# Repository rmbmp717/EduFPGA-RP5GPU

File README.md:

# EduFPGA-RP5GPU (Verilog HDL & C++ & Python)

## Introduction

EduFPGA-RP5GPU is an educational GPU designed to work with the Raspberry Pi 5.  
The design data runs on the FPGA and includes a PCIe controller.  
Communication with the Raspberry Pi 5 is possible via a PCIe driver.  
The project includes a PCIe driver compatible with the Raspberry Pi 5 and sample Python scripts.

*Note: This project was created for educational and experimental purposes. Product-grade features and performance improvements will be considered in the future.*

## Demo Environment
- Demo setup
- Raspberry Pi 5 + Tang Mega 138K + PCIe adapter board + ASM1182e PCIe repeater board <br>

- ASM1182e PCIe repeater board
- Without using the ASM1182e PCIe repeater board, the Gowin FPGA's PCIe IP is not recognized at RP5 startup.<br>

## GPU
- The design is based on the tiny-gpu project by the following author:
https://github.com/adam-maj/tiny-gpu
- The ISA (instruction set architecture) has been extended to include a floating-point multiplication instruction.
- GPU ISA <br>

## Directories
- GPU design data runnable on FPGA.
- Includes PCIe controller design data runnable on FPGA.
- PCIe driver code compilable on Raspberry Pi 5.
- Sample Python script to operate the GPU.

## Block Diagram
- Overall block diagram <br>

## Delivered Artifacts
- GPU design data (Verilog)
- GPU data memory controller (Verilog)
- Demo board design (KiCAD)
- PCIe driver (C++)
- FPGA-side PCIe controller (Verilog)
- Python program for character image recognition demo
- PCIe Write/Read program (C++)

## Demo Results
- Ran character recognition code on the Raspberry Pi 5.
- Data is transferred to the GPU via PCIe, and DL operations are executed.
- Character image recognition result when running EduGPU_mnist.py <br>

## PCIe IP Settings
- The PCIe IP BAR settings are as follows: <br>

| BAR  | Enabled | Type    | 64 bit | Prefetchable | Size         | Value (Hex) |
|------|---------|---------|--------|--------------|--------------|-------------|
| Bar0 | Yes     | Memory  | Yes    | No           | 1 Kilobyte   | FFFFFC00    |
| Bar2 | Yes     | Memory  | Yes    | No           | 64 Kilobytes | FFFF0000    |
| Bar4 | Yes     | Memory  | Yes    | No           | 2 Kilobytes  | FFFFF800    |

## Demo Board
- Although the tang console has now been released and I no longer plan to use this, I designed a board that can accommodate FPGA sub-boards.
- Designed with KiCAD.
- Compatible with the Tang 138K SOM board.
- (There are wiring correction points)

## Unresolved Issues
- DMA transfer is not yet supported.
- The design has not progressed to the point of using the DDR memory on the FPGA board concurrently with the GPU.

## Future Plans
- After completing minimal operation checks, I consulted with someone at the Sapporo Small and Medium Enterprise Center, and the conclusion was that "it would be difficult to commercialize" (I had explained from the start that this was for educational purposes).
- Once the Sipeed FPGA board (tang console) arrives from a Chinese online store as a replacement for the demo board, I plan to write the existing design data to it, confirm operation, and then wrap up the project.

## Impressions
- I have compiled the past Notes and design data.
- The design period was 2.5 months.
- If you don’t organize things from a year ago, you tend to forget them.

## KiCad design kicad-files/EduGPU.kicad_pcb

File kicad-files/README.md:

# Demo Board

- Although the tang console has now been released and I no longer plan to use this, I designed a board that can accommodate FPGA sub-boards.
- Designed with KiCAD.
- (There are wiring correction points) <br>

- Compatible with the Tang 138K SOM board. <br>

- SOM Back side. <br>

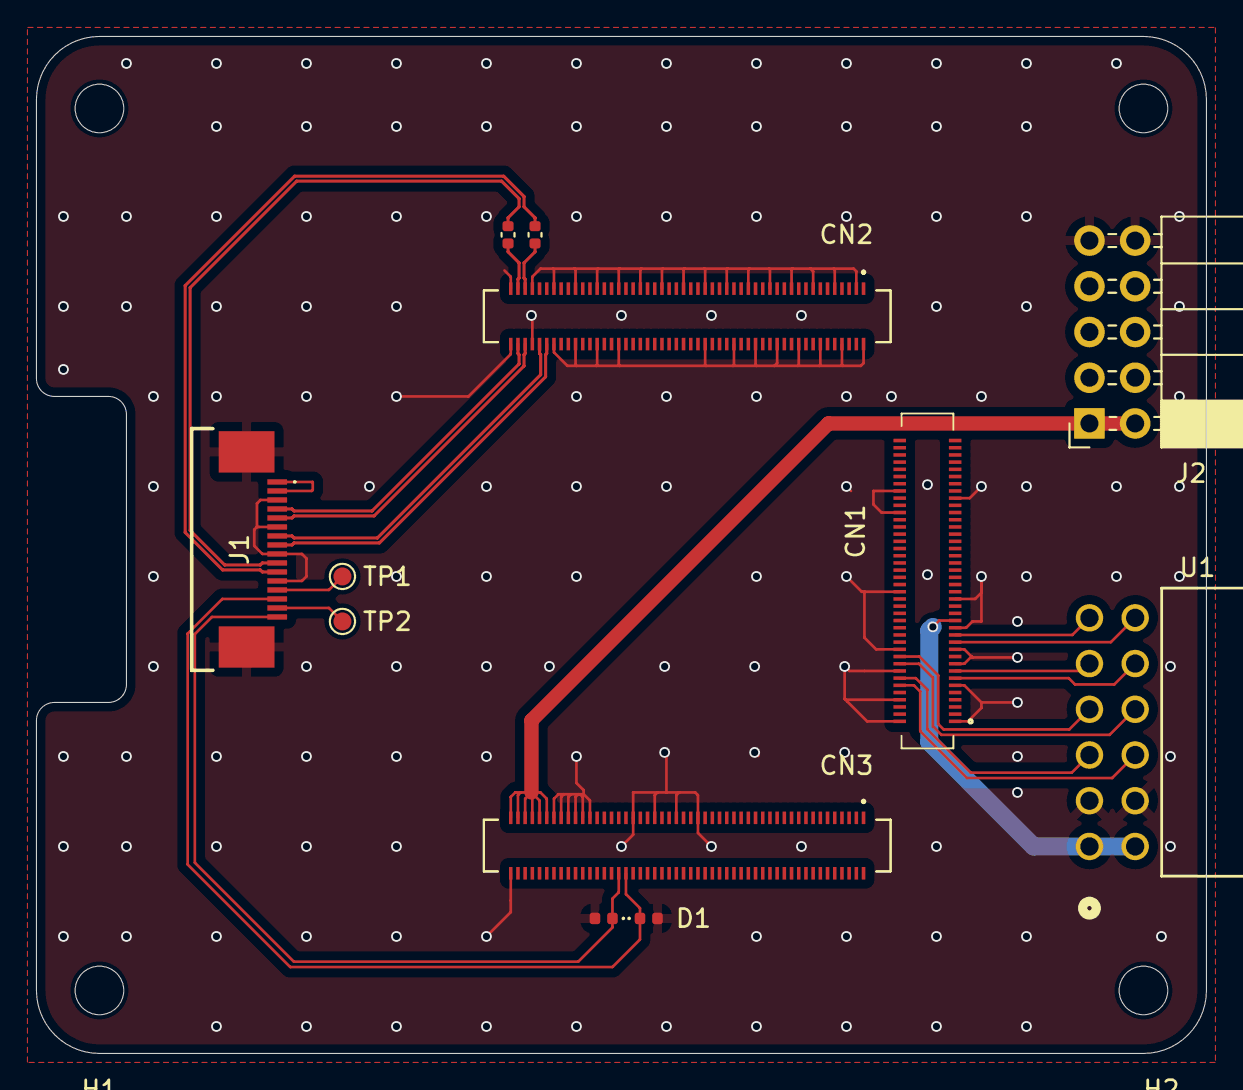
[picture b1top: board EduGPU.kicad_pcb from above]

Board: 4 copper layers, 65.0 x 56.5 mm, 16 parts (0 on the bottom side), 24 nets.

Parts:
C1, C2: GCM155R71C154KE02D; C_0402_1005Metric
CN1: DF40C-80DS-0.4V_58_; DF40C80DS04V58
CN2, CN3: DF40C-100DS-0.4V_58_; DF40C100DS04V58
D1, D2: LXES15AAA1-153; D_0402_1005Metric
H1, H2, H3, H4: MountingHole; MountingHole_2.7mm_M2.5
J1: 1-1734839-6; 117348396
J2: SSW-105-02-G-D; PinSocket_2x05_P2.54mm_Horizontal
TP1: PWR_EN; TestPoint_Pad_D1.0mm
TP2: PCIE_CLKREQ_N; TestPoint_Pad_D1.0mm
U1: PPPC062LJBN-RC; CONN_PPPC062LJBN-RC_SUL_OddEven

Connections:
+3V3: CN1.29, U1.1, U1.2
/PCIE_CLKREQ_N: J1.15, TP2.1
/PWR_EN: J1.13, TP1.1
/TX_N: C1.2, CN2.95
/TX_P: C2.2, CN2.97
DET_WAKE: CN3.68, D1.1, J1.14
GND: CN1.1, CN1.2, CN1.8, CN1.11, CN1.16, CN1.17, CN1.21, CN1.22, CN1.27, CN1.35, CN1.38, CN1.60, CN1.63, CN1.66, CN2.2, CN2.3, CN2.8, CN2.9, CN2.14, CN2.15, CN2.20, CN2.21, CN2.26, CN2.27, CN2.32, CN2.33, CN2.38, CN2.39, CN2.45, CN2.46, CN2.51, CN2.57, CN2.63, CN2.69, CN2.70, CN2.75, CN2.76, CN2.81, CN2.82, CN2.87, CN2.88, CN2.93, CN2.94, CN2.99, CN2.100, CN3.47, CN3.53, CN3.59, CN3.65, CN3.77, CN3.79, CN3.81, CN3.83, CN3.85, CN3.87, CN3.100, D1.2, D2.2, J1.3, J1.6, J1.9, J1.12, J1.17 (MP1), J1.18 (MP2), J2.9, J2.10, U1.3, U1.4
PCIE+5V: J1.1, J1.2
PCIE_CLK_N: CN2.96, J1.5
PCIE_CLK_P: CN2.98, J1.4
PCIE_RST: CN3.70, D2.1, J1.16
PCIE_RX_N: CN2.90, J1.8
PCIE_RX_P: CN2.92, J1.7
PCIE_TX_N: C1.1, J1.11
PCIE_TX_P: C2.1, J1.10
PMOD_IO0: CN1.25, U1.11
PMOD_IO1: CN1.23, U1.12
PMOD_IO2: CN1.15, U1.9
PMOD_IO3: CN1.13, U1.10
PMOD_IO4: CN1.20, U1.7
PMOD_IO5: CN1.18, U1.8
PMOD_IO6: CN1.14, U1.5
PMOD_IO7: CN1.12, U1.6
VCC+5V: CN3.89, CN3.91, CN3.93, CN3.95, CN3.97, CN3.99, J2.1, J2.2

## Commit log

2025-04-25 Rename pcie_tlp_packet_dec .v to pcie_tlp_packet_dec.v
2025-04-25 Rename EduGraphics_GPU_ASM.py to EduFPGA_RP5GPU_ASM.py
2025-05-09 Rename FPGA_top.v to EduFPGA_top.v
2025-05-10 Rename FPGA_DDR/FPGA_DDR/.gitkeep to FPGA_DDR/.gitkeep
2025-05-10 Rename EduGraphics_LCD_Controller.v to EduFPGA_LCD_Controller.v
2025-05-10 Rename EduGraphics_GPU_ASM.py to EduGPU_Assembler.py
2025-05-10 Rename GPU_Neuralnet.py to EduGPU_mnist.py
2025-05-11 Rename EduFPGA_RP5GPU_ASM.py to EduGPU_Assembler.py
